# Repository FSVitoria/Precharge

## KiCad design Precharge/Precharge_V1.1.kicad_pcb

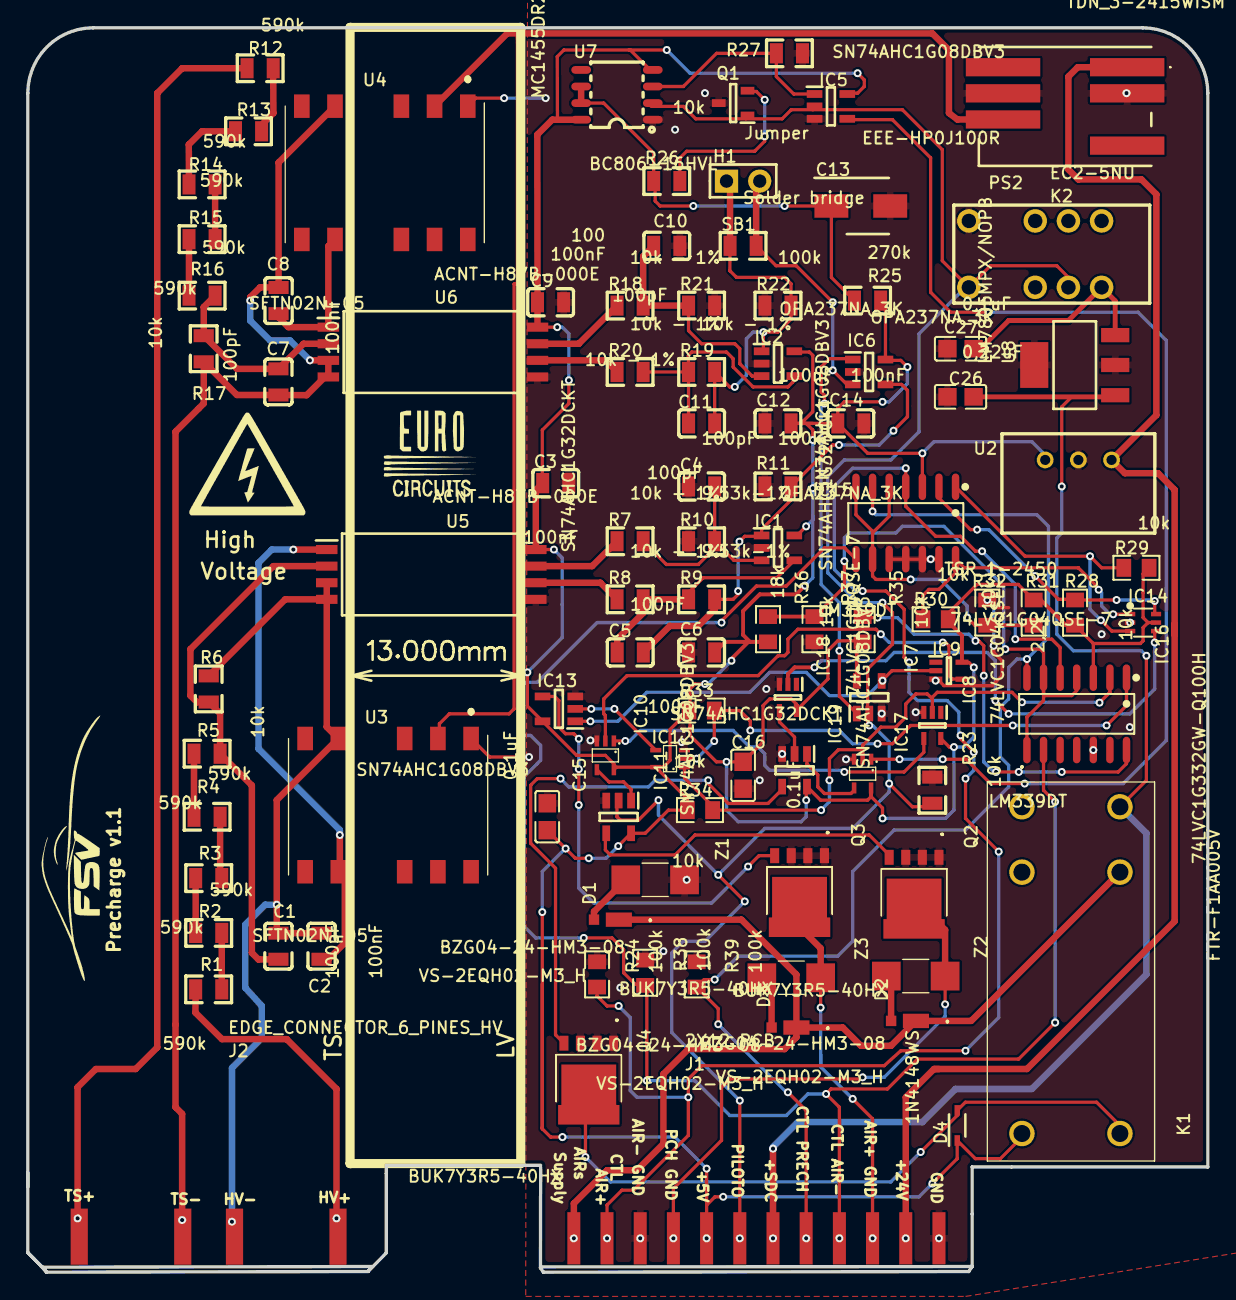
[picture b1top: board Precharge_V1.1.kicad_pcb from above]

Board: 2 copper layers, 90.3 x 95.2 mm, 99 parts (0 on the bottom side), 68 nets.

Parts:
C1, C4, C5, C7, C10, C11: 100pF; C0805
C2, C3, C6, C8, C9, C12, C14: 100nF; C0805
C13: EEE-HP0J100R; CAPAE430X610N
C15, C16: 0.1uF; C0805
C26: 0,22uF; C0805
C27: 0,1uF; C0805
D1, D2, D3: VS-2EQH02-M3_H; VS2EQH02M3H
D4: 1N4148WS; SODFL2512X90N
H1: Jumper; 2P COPY
IC1, IC2, IC6: OPA237NA_3K; SOT95P280X145-5N
IC5, IC7, IC11, IC13, IC19: SN74AHC1G08DBV3; SOT95P280X145-5N
IC8, IC9, IC18: 74LVC1G04QSE-7; SOT65P210X100-5N
IC10, IC12, IC17: SN74AHC1G32DCKT; SC-70-5_L2.0-W1.3-P0.65-LS2.1-BR
IC14: 74LVC1G332GW-Q100H; SOT-363_L2.0-W1.3-P0.65-LS2.1-BL
IC15, IC16: LM339DT; SOIC-14_L8.7-W3.9-P1.27-LS6.0-BL
J1: 2X12 PCB; PRECH_LV_CONNECTOR
J2: EDGE_CONNECTOR_6_PINES_HV
K1: FTR-F1AA005V; FTRF1AA005V
K2: EC2-5NU; RELAY-TH_EC2-XXXX
PS2: TDN_3-2415WISM; TDN32415WISM
Q1: BC806-16HVL; SOT95P230X110-3N
Q2, Q3, Q4: BUK7Y3R5-40HX; BUK7Y3R540HX
R1, R2, R3, R4, R5, R12, R13, R14, R15, R16: 590k; R0805
R6, R17, R23, R27: 10k; R0805
R7, R8, R18, R19, R20, R21: 10k - 1%; R0805
R9, R10: 9.53k-1%; R0805
R11, R22: 100k; R0805
R24, R38, R39: 100k; R0805_NEW
R25: 270k; R0805
R26: 100; R0805
R28, R29, R30, R31, R33, R34, R35, R36: 10k; R0805_NEW
R32: 2,2k; R0805_NEW
R37: 18k; R0805_NEW
SB1: Solder bridge; R0805
U2: TSR_1-2450; TSR-1-24120
U3, U4: SFTN02N-05; SFTN02N12
U5, U6: ACNT-H87B-000E; SOIC127P1661X373-8N
U7: MC1455DR2G; SOIC-8_L4.9-W3.9-P1.27-LS6.0-BL
U8: LM7805MPX/NOPB; SOT-223
Z1, Z2, Z3: BZG04-24-HM3-08; BZG0424HM308

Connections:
+5V: C3.2, C6.1, C9.1, C12.2, C14.1, C15.1, C16.1, D4.1, IC1.5, IC2.5, IC5.5, IC6.5, IC7.5, IC8.5, IC9.5, IC10.5, IC11.5, IC12.5, IC13.5, IC14.5, IC15.3, IC16.3, IC17.5, IC18.5, IC19.5, J1.A5, J1.B5, K1.4, R25.2, R28.2, R29.2, R30.2, R31.2, R33.2, R34.2, R35.2, R36.2, U2.3, U5.8, U6.8, U7.4, U7.8
+5VISOHV: C2.2, U3.8, U5.1
+5VISOTS: C8.2, U4.8, U6.1
+24V: J1.A11, J1.B11, PS2.1, U2.1
+24V_ESTABLES: PS2.7, U3.2, U4.2
C1_2: C1.2, R5.1, R6.2, U5.2
C4_2: C4.2, IC1.3, R7.2, R10.2
C5_1: C5.1, IC1.4, R8.2, R9.1
C7_2: C7.2, R16.2, R17.2, U6.2
C27_2: C27.2, K2.5, U8.3
CONTROL_AIR+: IC15.4, IC16.5, J1.A2, J1.B2, R24.2
CONTROL_AIR-: IC15.8, IC16.9, J1.A9, J1.B9, R38.2
CONTROL_AIR_PRE: IC15.6, IC16.7, J1.A8, J1.B8, R39.2
D4_2: D4.2, K1.5, Q4.5, Q4.6
ESTADO_AIR+: IC8.2, IC12.1, IC16.2, IC17.2, R34.1
ESTADO_AIR-: IC16.14, R35.1
ESTADO_AIR_PRE: IC12.2, IC16.1, R33.1
GND: C3.1, C4.1, C6.2, C9.2, C10.1, C12.1, C13.2, C14.2, C15.2, C16.2, C26.1, C27.1, IC1.2, IC2.2, IC5.3, IC6.2, IC7.3, IC8.3, IC9.3, IC10.3, IC11.3, IC12.3, IC13.3, IC14.2, IC15.10, IC15.11, IC15.12, IC15.13, IC16.12, IC17.3, IC18.3, IC19.3, J1.A3, J1.A12, J1.B3, J1.B12, K2.12, PS2.2, PS2.6, Q1.3, Q2.1, Q2.2, Q2.3, Q3.1, Q3.2, Q3.3, Q4.1, Q4.2, Q4.3, R10.1, R11.1, R21.1, R22.1, R23.1, R24.1, R27.1, R32.1, R37.1, R38.1, R39.1, U2.2, U3.1, U4.1, U5.5, U6.5, U7.1, U8.2, U8.4, Z1.1
HV+: J2.A6, J2.B6, R1.2
HV-: C1.1, C2.1, J2.A4, J2.B4, R6.1, U3.5, U5.3, U5.4
IC8_4: IC8.4, IC10.1
IC9_2: IC7.4, IC9.2, IC13.1
IC9_4: IC9.4, IC10.2
IC11_1: IC10.4, IC11.1
IC13_2: IC12.4, IC13.2
IC14_1: IC14.1, IC15.14, R30.1
IC14_3: IC14.3, IC15.1, R29.1
IC14_6: IC14.6, IC15.2, R28.1
IC15_9: IC15.5, IC15.7, IC15.9, R31.1, R32.2
IC19_1: IC17.4, IC19.1
IC19_2: IC18.4, IC19.2
N_AIR+: J1.A10, J1.B10, Q3.5, Q3.6, Z3.1
N_R_PRE: J1.A4, J1.B4, Q2.5, Q2.6, Z2.1
PILOTO: IC5.2, IC7.2, IC11.2, J1.A6, J1.B6, K2.1, K2.4, Q1.1, R23.2, U7.2
Q2_4: IC11.4, Q2.4
Q3_4: IC13.4, Q3.4
Q4_4: IC19.4, Q4.4
R2_2: R1.1, R2.2
R3_2: R2.1, R3.2
R4_2: R3.1, R4.2
R5_2: R4.1, R5.2
R7_1: R7.1, U5.7
R8_1: R8.1, U5.6
R13_1: R12.2, R13.1
R14_1: R13.2, R14.1
R15_1: R14.2, R15.1
R16_1: R15.2, R16.1
R18_1: R18.1, U6.7
R20_1: R20.1, U6.6
R20_2: C11.2, IC2.4, R19.1, R20.2
R21_2: C10.2, IC2.3, R18.2, R21.2
R25_1: C13.1, R25.1, R26.2, U7.6, U7.7
R26_1: Q1.2, R26.1
R27_2: IC5.1, R27.2, U7.3
R37_2: IC16.4, IC16.6, IC16.8, R36.1, R37.2
RELAY_FAULT: IC14.4, IC18.2
SB1_2: H1.2, IC6.3, SB1.2
SDC_AIRS_SUPPLY: D1.1, D2.1, D3.1, J1.A1, J1.B1, K1.7
SDC_AIRS_SUPPLY_IN: C26.2, J1.A7, J1.B7, K1.8, U8.1
TIMER: IC5.4, IC17.1
TS+: J2.A1, J2.B1, R12.1
TS-: C7.1, C8.1, J2.A3, J2.B3, R17.1, U4.5, U6.3, U6.4
V_BATT: C5.2, IC1.1, IC6.4, R9.2, R11.2
V_COMP: IC6.1, IC7.1
V_TS: C11.1, H1.1, IC2.1, R19.2, R22.2, SB1.1
Z1_2: D1.2, Z1.2
Z2_2: D2.2, Z2.2
Z3_2: D3.2, Z3.2
